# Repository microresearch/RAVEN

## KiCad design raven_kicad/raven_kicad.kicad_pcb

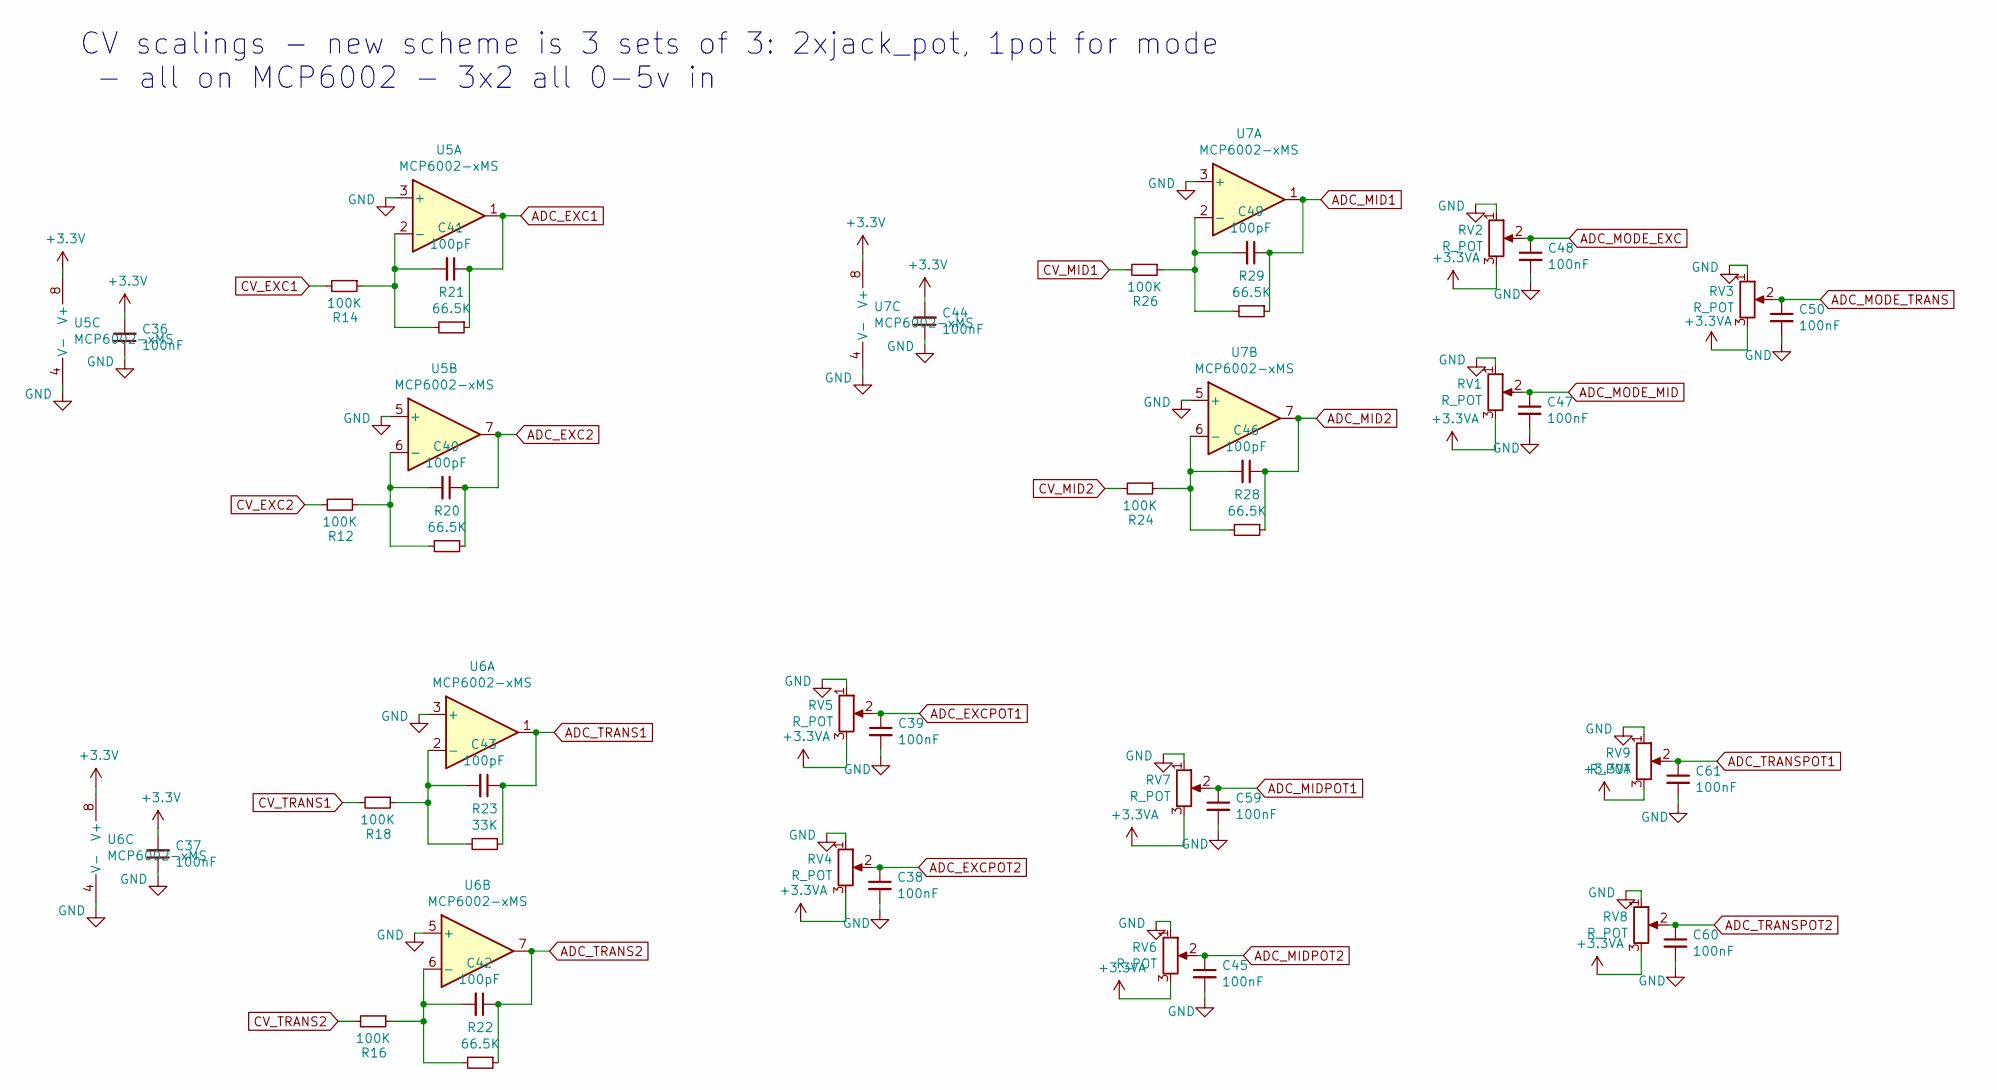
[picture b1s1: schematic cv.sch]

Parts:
C36, C37, C38, C39, C44, C45, C47, C48, C50, C59, C60, C61: 100nF; C_0805
C40, C41, C42, C43, C46, C49: 100pF; C_0805
R12, R14, R16, R18, R24, R26: 100K; R_0805
R20, R21, R22, R28, R29: 66.5K; R_0805
R23: 33K; R_0805
RV1, RV2, RV3, RV4, RV5, RV6, RV7, RV8, RV9: R_POT; Potentiometer_Alps-RK09
U5, U6, U7: MCP6002-xMS; SOIC-8-N

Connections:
+3.3VA: RV1.3, RV2.3, RV3.3, RV4.3, RV5.3, RV6.3, RV7.3, RV8.3, RV9.3; also elsewhere on the board
+3V3: C36.2, C37.2, C44.2, U5.8 (V+), U6.8 (V+), U7.8 (V+); also elsewhere on the board
ADC_EXC1: C41.1, R21.1, U5.1; also elsewhere on the board
ADC_EXC2: C40.1, R20.1, U5.7; also elsewhere on the board
ADC_EXCPOT1: C39.1, RV5.2; also elsewhere on the board
ADC_EXCPOT2: C38.1, RV4.2; also elsewhere on the board
ADC_MID1: C49.1, R29.1, U7.1; also elsewhere on the board
ADC_MID2: C46.1, R28.1, U7.7; also elsewhere on the board
ADC_MIDPOT1: C59.1, RV7.2; also elsewhere on the board
ADC_MIDPOT2: C45.1, RV6.2; also elsewhere on the board
ADC_MODE_EXC: C48.1, RV2.2; also elsewhere on the board
ADC_MODE_MID: C47.1, RV1.2; also elsewhere on the board
ADC_MODE_TRANS: C50.1, RV3.2; also elsewhere on the board
ADC_TRANS1: C43.1, R23.1, U6.1; also elsewhere on the board
ADC_TRANS2: C42.1, R22.1, U6.7; also elsewhere on the board
ADC_TRANSPOT1: C61.1, RV9.2; also elsewhere on the board
ADC_TRANSPOT2: C60.1, RV8.2; also elsewhere on the board
CV_EXC1: R14.2; also elsewhere on the board
CV_EXC2: R12.2; also elsewhere on the board
CV_MID1: R26.2; also elsewhere on the board
CV_MID2: R24.2; also elsewhere on the board
CV_TRANS1: R18.2; also elsewhere on the board
CV_TRANS2: R16.2; also elsewhere on the board
GND: C36.1, C37.1, C38.2, C39.2, C44.1, C45.2, C47.2, C48.2, C50.2, C59.2, C60.2, C61.2, RV1.1, RV2.1, RV3.1, RV4.1, RV5.1, RV6.1, RV7.1, RV8.1, RV9.1, U5.3 (+), U5.4 (V-), U5.5 (+), U6.3 (+), U6.4 (V-), U6.5 (+), U7.3 (+), U7.4 (V-), U7.5 (+); also elsewhere on the board
unnamed 49: C40.2, R12.1, R20.2, U5.6 (-); also elsewhere on the board
unnamed 50: C41.2, R14.1, R21.2, U5.2 (-); also elsewhere on the board
unnamed 51: C42.2, R16.1, R22.2, U6.6 (-); also elsewhere on the board
unnamed 52: C43.2, R18.1, R23.2, U6.2 (-); also elsewhere on the board
unnamed 53: C46.2, R24.1, R28.2, U7.6 (-); also elsewhere on the board
unnamed 54: C49.2, R26.1, R29.2, U7.2 (-); also elsewhere on the board

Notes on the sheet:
CV scalings - new scheme is 3 sets of 3: 2xjack_pot, 1pot for mode - all on MCP6002 - 3x2 all 0-5v in

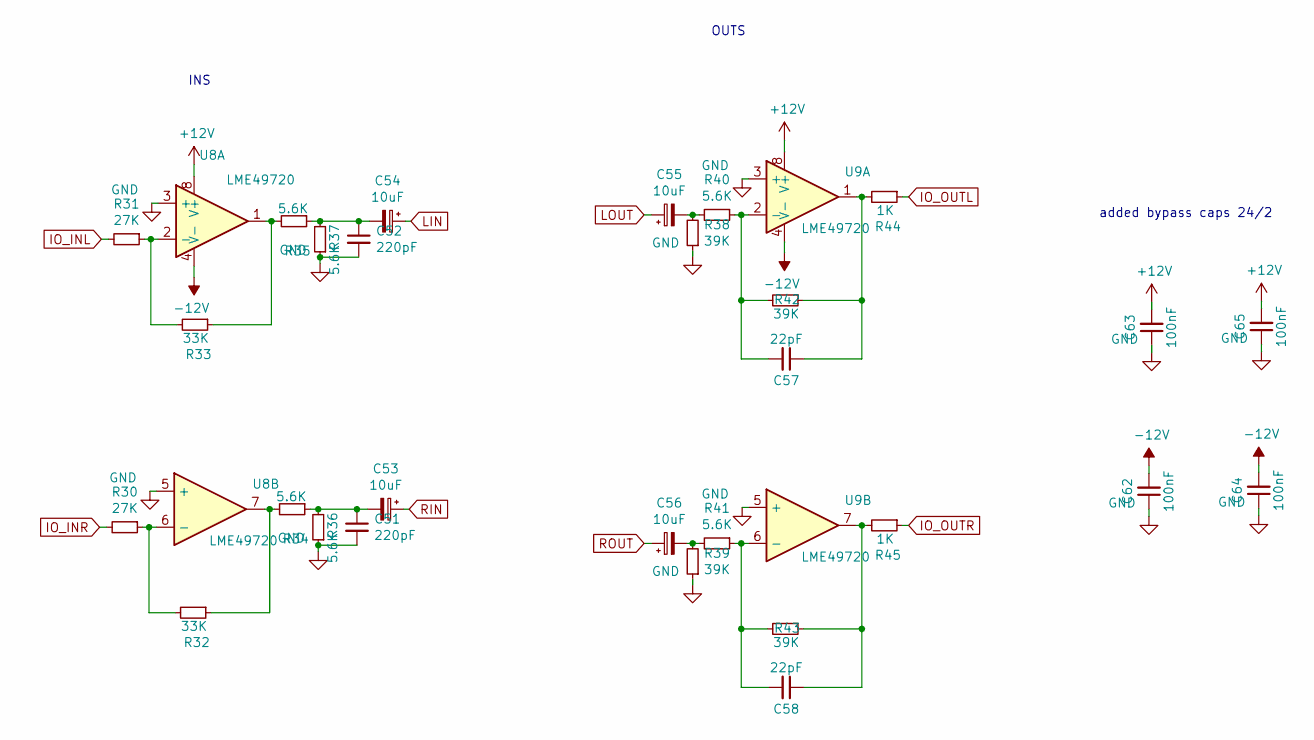
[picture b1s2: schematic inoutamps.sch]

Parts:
C51, C52: 220pF; C_0805
C53, C54, C55, C56: 10uF; SMD-1206_Pol
C57, C58: 22pF; C_0805
C62, C63, C64, C65: 100nF; C_0805
R30, R31: 27K; R_0805
R32, R33: 33K; R_0805
R34, R35, R36, R37, R40, R41: 5.6K; R_0805
R38, R39, R42, R43: 39K; R_0805
R44, R45: 1K; R_0805
U8, U9: LME49720; SOIC-8-N

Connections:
+12V: C63.2, C65.2, U8.8 (V+), U9.8 (V+); also elsewhere on the board
-12V: C62.2, C64.2, U8.4 (V-), U9.4 (V-); also elsewhere on the board
GND: C51.2, C52.2, C62.1, C63.1, C64.1, C65.1, R36.1, R37.1, R38.1, R39.1, U8.3 (+), U8.5 (+), U9.3 (+), U9.5 (+); also elsewhere on the board
IO_INL: R31.2; also elsewhere on the board
IO_INR: R30.2; also elsewhere on the board
IO_OUTL: R44.1; also elsewhere on the board
IO_OUTR: R45.1; also elsewhere on the board
LIN: C54.1; also elsewhere on the board
LOUT: C55.1; also elsewhere on the board
unnamed: C51.1, C53.2, R34.1, R36.2
unnamed: C52.1, C54.2, R35.1, R37.2
unnamed: C55.2, R38.2, R40.2
unnamed: C56.2, R39.2, R41.2
unnamed: C57.1, R42.1, R44.2, U9.1
unnamed: C57.2, R40.1, R42.2, U9.2 (-)
unnamed: C58.1, R43.1, R45.2, U9.7
unnamed: C58.2, R41.1, R43.2, U9.6 (-)
unnamed: R30.1, R32.2, U8.6 (-)
unnamed: R31.1, R33.2, U8.2 (-)
unnamed: R32.1, R34.2, U8.7
unnamed: R33.1, R35.2, U8.1
RIN: C53.1; also elsewhere on the board
ROUT: C56.1; also elsewhere on the board

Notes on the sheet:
INS
OUTS
added bypass caps 24/2

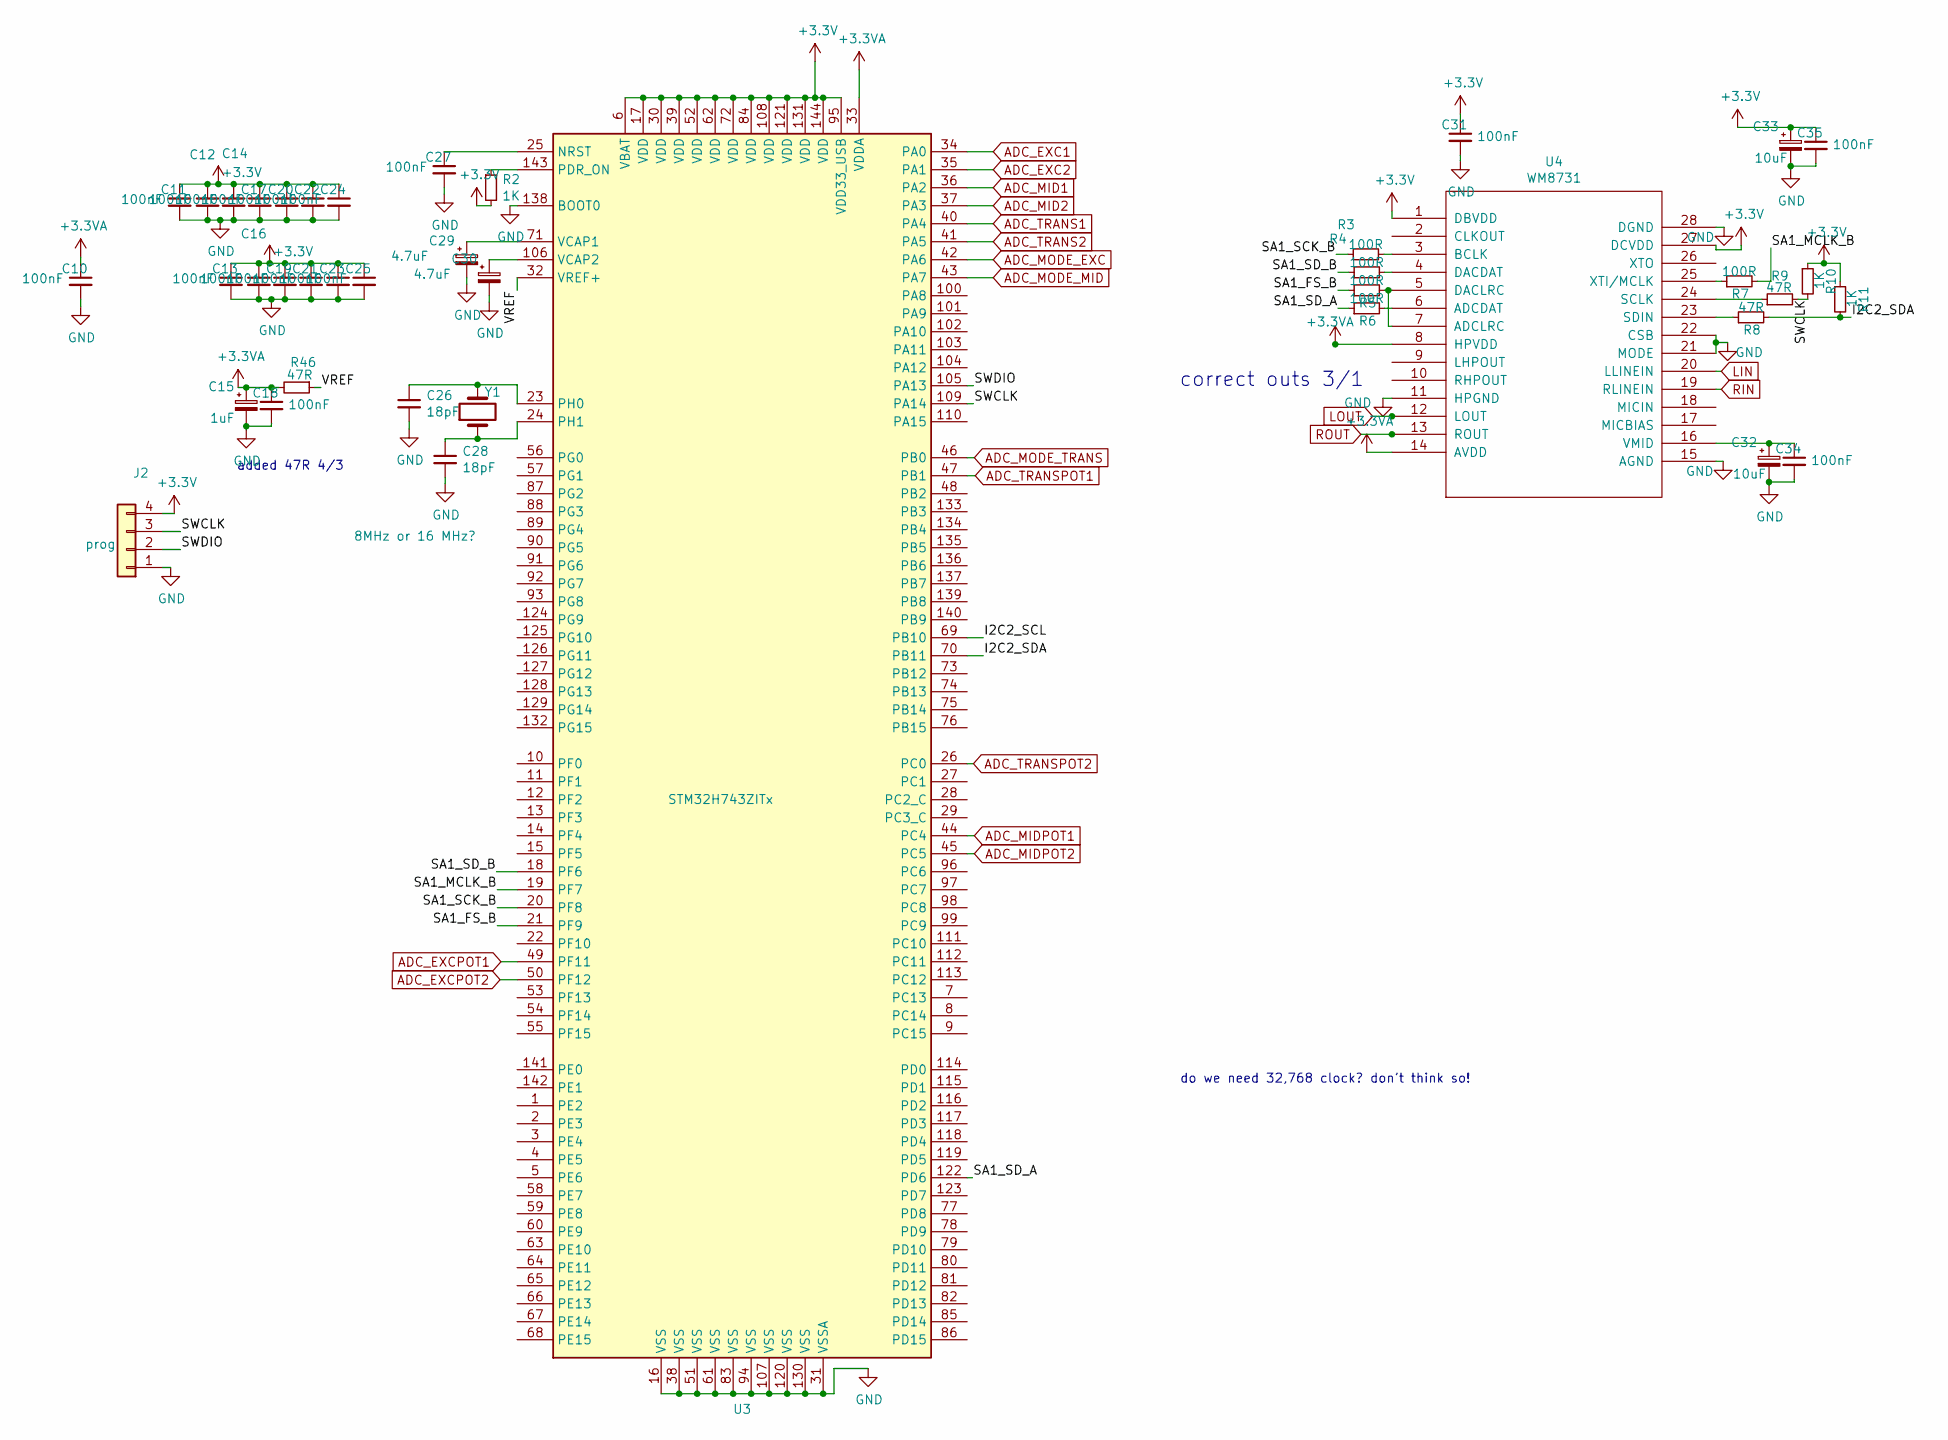
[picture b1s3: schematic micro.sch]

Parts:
C10, C11, C12, C13, C14, C16, C17, C18, C19, C20, C21, C22, C23, C24, C25, C27, C31, C34, C35: 100nF; C_0805
C15: 1uF; SMD-1206_Pol
C26, C28: 18pF; C_0805
C29, C30: 4.7uF; SMD-1206_Pol
C32, C33: 10uF; SMD-1206_Pol
J2: prog; Pin_Header_Straight_1x04_Pitch2.54mm
R2, R10, R11: 1K; R_0805
R3, R4, R5, R6, R7: 100R; R_0805
R8, R9, R46: 47R; R_0805
U3: STM32H743ZITx; LQFP-144_20x20mm_Pitch0.5mm
U4: WM8731; SSOP-28_5.3x10.2mm_Pitch0.65mm
Y1: 8MHz or 16 MHz?; Crystal_SMD_HC49-SD

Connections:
+3.3VA: C10.1, C15.1, C18.1, R46.2, U3.33 (VDDA), U4.8 (HPVDD), U4.14 (AVDD); also elsewhere on the board
+3V3: C11.1, C12.1, C13.1, C14.1, C16.1, C17.1, C19.1, C20.1, C21.1, C22.1, C23.1, C24.1, C25.1, C31.1, C33.1, C35.1, J2.4, R2.2, R10.1, R11.1, U3.6 (VBAT), U3.17 (VDD), U3.30 (VDD), U3.39 (VDD), U3.52 (VDD), U3.62 (VDD), U3.72 (VDD), U3.84 (VDD), U3.95 (VDD33_USB), U3.108 (VDD), U3.121 (VDD), U3.131 (VDD), U3.144 (VDD), U4.1 (DBVDD), U4.27 (DCVDD); also elsewhere on the board
/micro/I2C2_SDA: R8.2, R11.2, U3.70 (PB11)
/micro/SA1_FS_B: R5.1, U3.21 (PF9)
/micro/SA1_MCLK_B: R7.2, U3.19 (PF7)
/micro/SA1_SCK_B: R3.1, U3.20 (PF8)
/micro/SA1_SD_A: R6.1, U3.122 (PD6)
/micro/SA1_SD_B: R4.1, U3.18 (PF6)
/micro/SWCLK: J2.3, R9.2, R10.2, U3.109 (PA14)
/micro/SWDIO: J2.2, U3.105 (PA13)
/micro/VREF: R46.1, U3.32 (VREF+)
ADC_EXC1: U3.34 (PA0); also elsewhere on the board
ADC_EXC2: U3.35 (PA1); also elsewhere on the board
ADC_EXCPOT1: U3.49 (PF11); also elsewhere on the board
ADC_EXCPOT2: U3.50 (PF12); also elsewhere on the board
ADC_MID1: U3.36 (PA2); also elsewhere on the board
ADC_MID2: U3.37 (PA3); also elsewhere on the board
ADC_MIDPOT1: U3.44 (PC4); also elsewhere on the board
ADC_MIDPOT2: U3.45 (PC5); also elsewhere on the board
ADC_MODE_EXC: U3.42 (PA6); also elsewhere on the board
ADC_MODE_MID: U3.43 (PA7); also elsewhere on the board
ADC_MODE_TRANS: U3.46 (PB0); also elsewhere on the board
ADC_TRANS1: U3.40 (PA4); also elsewhere on the board
ADC_TRANS2: U3.41 (PA5); also elsewhere on the board
ADC_TRANSPOT1: U3.47 (PB1); also elsewhere on the board
ADC_TRANSPOT2: U3.26 (PC0); also elsewhere on the board
GND: C10.2, C11.2, C12.2, C13.2, C14.2, C15.2, C16.2, C17.2, C18.2, C19.2, C20.2, C21.2, C22.2, C23.2, C24.2, C25.2, C26.2, C27.2, C28.2, C29.2, C30.2, C31.2, C32.2, C33.2, C34.2, C35.2, J2.1, U3.16 (VSS), U3.31 (VSSA), U3.38 (VSS), U3.51 (VSS), U3.61 (VSS), U3.83 (VSS), U3.94 (VSS), U3.107 (VSS), U3.120 (VSS), U3.130 (VSS), U3.138 (BOOT0), U4.11 (HPGND), U4.15 (AGND), U4.21 (MODE), U4.22 (CSB), U4.28 (DGND); also elsewhere on the board
LIN: U4.20 (LLINEIN); also elsewhere on the board
LOUT: U4.12 (LOUT); also elsewhere on the board
unnamed: C26.1, U3.23 (PH0), Y1.2
unnamed: C27.1, U3.25 (NRST)
unnamed: C28.1, U3.24 (PH1), Y1.1
unnamed: C29.1, U3.71 (VCAP1)
unnamed: C30.1, U3.106 (VCAP2)
unnamed: C32.1, C34.1, U4.16 (VMID)
unnamed: R2.1, U3.143 (PDR_ON)
unnamed: R3.2, U4.3 (BCLK)
unnamed: R4.2, U4.4 (DACDAT)
unnamed: R5.2, U4.5 (DACLRC), U4.7 (ADCLRC)
unnamed: R6.2, U4.6 (ADCDAT)
unnamed: R7.1, U4.25 (XTI/MCLK)
unnamed: R8.1, U4.23 (SDIN)
unnamed: R9.1, U4.24 (SCLK)
RIN: U4.19 (RLINEIN); also elsewhere on the board
ROUT: U4.13 (ROUT); also elsewhere on the board

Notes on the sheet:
do we need 32,768 clock? don't think so!
correct outs 3/1
added 47R 4/3

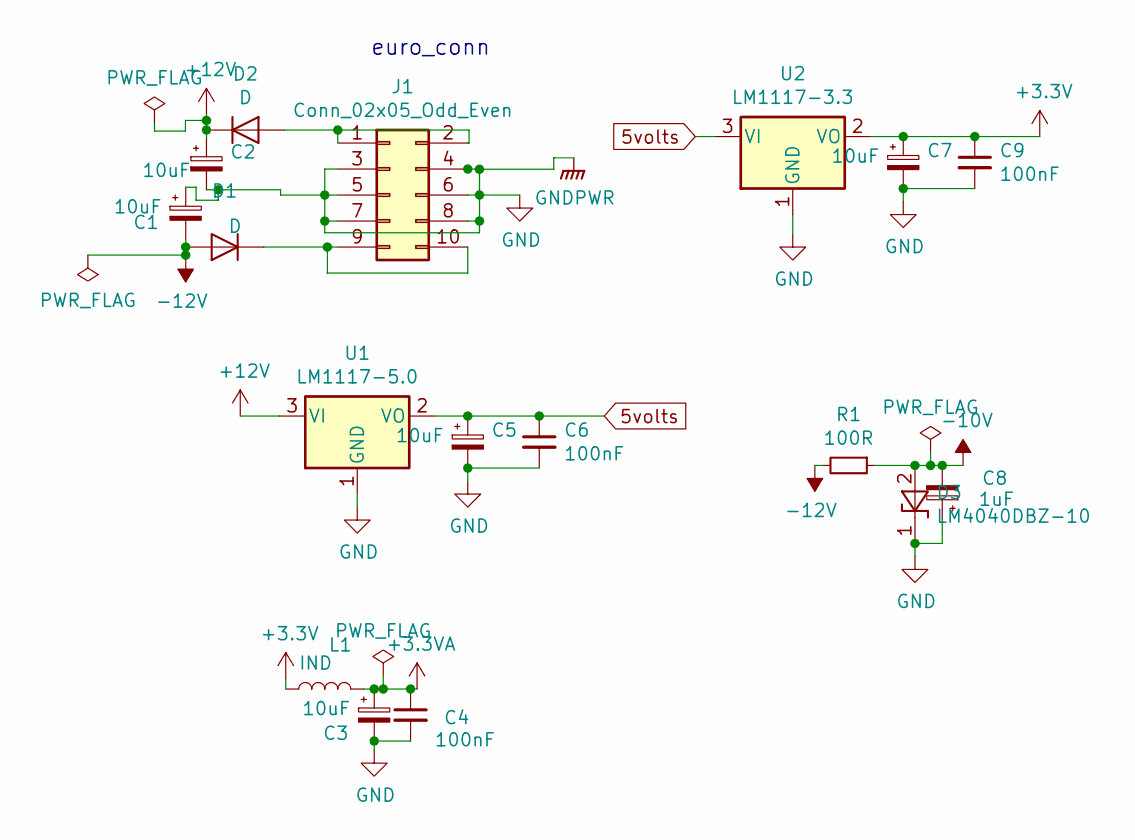
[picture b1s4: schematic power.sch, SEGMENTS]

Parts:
C1, C2, C3, C5, C7: 10uF; SMD-1206_Pol
C4, C6, C9: 100nF; C_0805
C8: 1uF; SMD-1206_Pol
D1, D2: D; D_SOD-123
D3: LM4040DBZ-10; SOT-23
J1: Conn_02x05_Odd_Even; Pin_Header_Straight_2x05_Pitch2.54mm
L1: IND; L_0603
R1: 100R; R_0805
U1: LM1117-5.0; TO-252-2_Rectifier
U2: LM1117-3.3; TO-252-2_Rectifier

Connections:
5volts: C5.1, C6.1, U1.2 (VO), U2.3 (VI)
+3.3VA: C3.1, C4.1, L1.2; also elsewhere on the board
+3V3: C7.1, C9.1, L1.1, U2.2 (VO); also elsewhere on the board
+12V: C2.1, D2.1 (K), U1.3 (VI); also elsewhere on the board
-10V: C8.2, D3.2 (A), R1.1; also elsewhere on the board
-12V: C1.2, D1.2 (A), R1.2; also elsewhere on the board
GND: C1.1, C2.2, C3.2, C4.2, C5.2, C6.2, C7.2, C8.1, C9.2, D3.1 (K), J1.3, J1.4, J1.5, J1.6, J1.7, J1.8, U1.1 (GND), U2.1 (GND); also elsewhere on the board
unnamed: D1.1 (K), J1.9, J1.10
unnamed: D2.2 (A), J1.1, J1.2

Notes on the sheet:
euro_conn

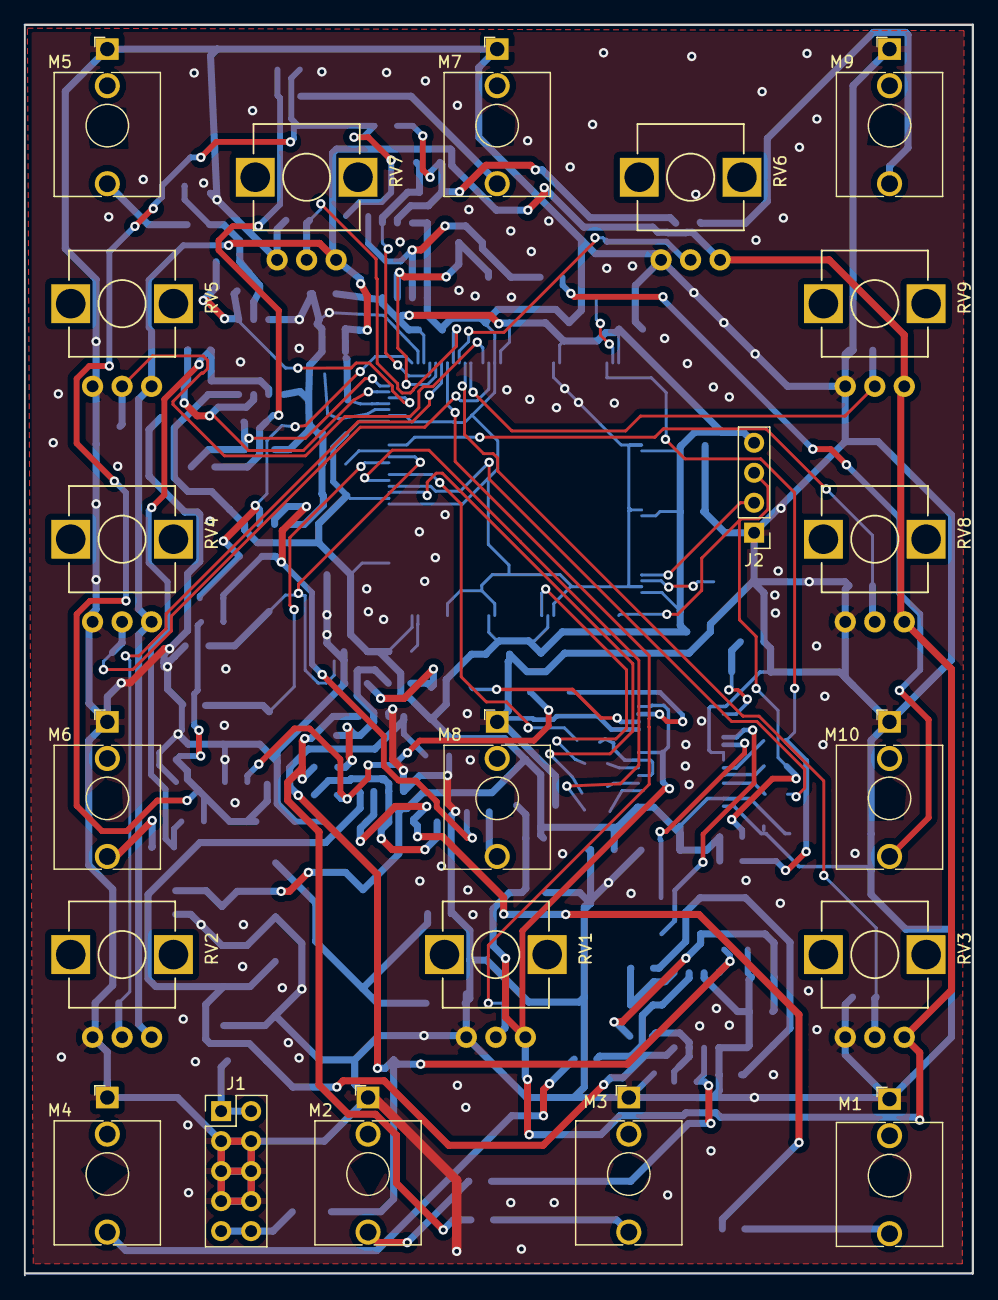
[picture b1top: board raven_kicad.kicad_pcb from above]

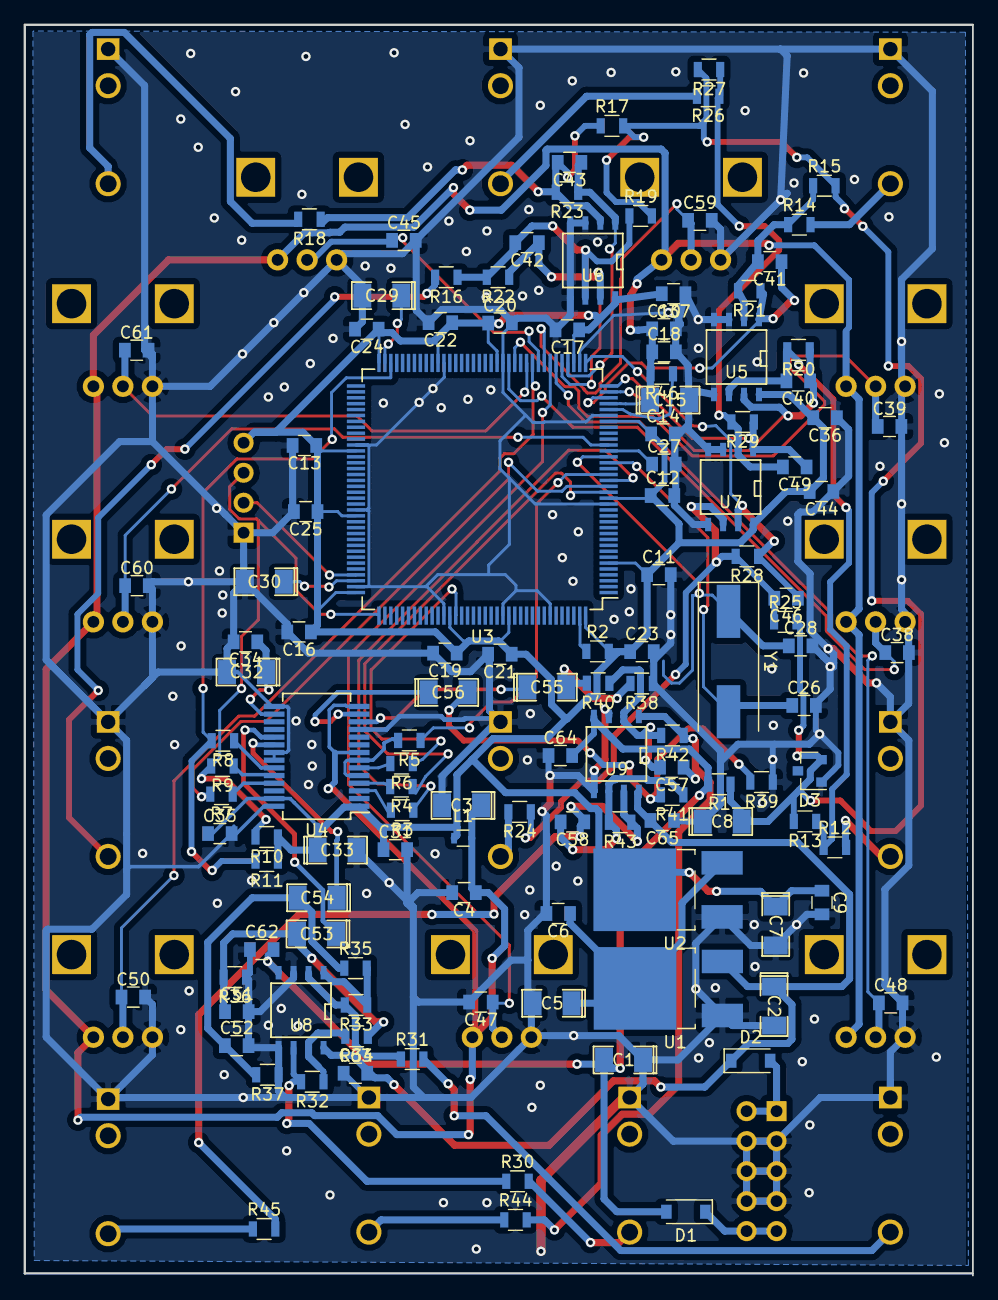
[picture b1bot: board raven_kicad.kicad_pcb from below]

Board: 2 copper layers, 80.3 x 105.9 mm, 146 parts (125 on the bottom side), 79 nets.

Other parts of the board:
M1, M2, M3, M4, M5, M6, M7, M8, M9, M10: AUDIO-JACKERTHENVAR; Jack_3.5mm_QingPu_WQP-PJ398SM_Vertical_CircularHoles
R13, R15, R17, R19, R25, R27: 200K; R_0805

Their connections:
-10V: R13.2, R15.2, R17.2, R19.2, R25.2, R27.2; also elsewhere on the board
CV_EXC1: M5.3; also elsewhere on the board
CV_EXC2: M6.3; also elsewhere on the board
CV_MID1: M7.3; also elsewhere on the board
CV_MID2: M8.3; also elsewhere on the board
CV_TRANS1: M9.3; also elsewhere on the board
CV_TRANS2: M10.3; also elsewhere on the board
GND: M1.1, M2.1, M3.1, M4.1, M5.1, M6.1, M7.1, M8.1, M9.1, M10.1; also elsewhere on the board
IO_INL: M4.3; also elsewhere on the board
IO_INR: M2.3; also elsewhere on the board
IO_OUTL: M3.3; also elsewhere on the board
IO_OUTR: M1.3; also elsewhere on the board
unnamed 49: R13.1; also elsewhere on the board
unnamed 50: R15.1; also elsewhere on the board
unnamed 51: R19.1; also elsewhere on the board
unnamed 52: R17.1; also elsewhere on the board
unnamed 53: R25.1; also elsewhere on the board
unnamed 54: R27.1; also elsewhere on the board

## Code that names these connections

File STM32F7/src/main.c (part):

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
*in hw_i2s.c -> look back to original code!*

    PF6     ------> SAI1_SD_B -> DACDAT = MOSI 
    PF7     ------> SAI1_MCLK_B -> MCLK on 8731 = 12.288MHz on board
    PF8     ------> SAI1_SCK_B -> BCLK = SCK on board
    PF9     ------> SAI1_FS_B -> DACLRC and ADCLRC = marked

    PD6     ------> SAI1_SD_A -> ADCDAT = MISO

    PB10     ------> I2C2_SCL -> SCLK 47R = SCL    PB11     ------> I2C2_SDA -> SDIN = SDA

 11/1/2021 failure and no signals on bus... causes:

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
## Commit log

2018-07-26 raven
2019-01-11 first
2019-09-11 lpc workings
2019-09-12 port ekext pure data pd
2019-09-13 added .flash to .ld as seemed need it now
2020-11-30 notes
2021-01-07 stm32f7
2021-01-11 tests for wm8731
2021-01-11 still no
2021-01-11 srong i2c
2021-01-11 progress?
2021-01-12 test spi code for h7
2021-01-12 still no sound
2021-01-13 8731 almost working
2021-01-14 8731 working so we need to clean up code a bit..
2021-01-18 32k now with changed clock
2021-01-19 process
2021-01-19 new notes finally
2021-01-20 waves?
2021-01-21 warps some
2021-02-01 slow porgress with H7 / nucleo
2021-02-01 closer
2021-02-02 SAI audio and STM32H743 finally working...
2021-02-03 vocoder works a bit, updated filters for 48k
2021-02-04 test
2021-02-15 TMSLIVE
2021-02-17 extra mind
2021-03-04 pcbb
